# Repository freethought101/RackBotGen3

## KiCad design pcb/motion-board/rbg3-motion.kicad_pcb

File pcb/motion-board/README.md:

# RBG3-MOTION v1 — robot motion board

2-layer, 100 × 100 mm module carrier: ESP32-S3-DevKitC-1 + 4 × TMC2209 StepStick drivers,
switch inputs, servo/LED/buzzer/I2C outputs, VMOT and dock voltage sensing.
Spec: [`docs/spec/02-electrical.md`](../../docs/spec/02-electrical.md) §3.

| File | What |
|---|---|
| `rbg3-motion.kicad_sch` / `.kicad_pcb` / `.kicad_pro` | KiCad 10 project (schematic ERC clean, DRC: 0 errors, 0 unconnected, 0 parity) |
| `lib/rbg3.kicad_sym`, `lib/rbg3.pretty/` | Custom symbols (`ESP32-S3-DevKitC-1`, `StepStick_TMC2209`) and the DevKit socket footprint |
| `scripts/build.sh` | Rebuilds the layout from scratch: text fix-ups → placement → silkscreen (`silk.py`) → antenna keep-out → Freerouting (GND routed as tracks too, so traces cannot cut a pour pocket loose) → stitching vias → pours → DRC; fails on unrouted nets or any error-level DRC item |
| `fab/rbg3-motion-gerbers.zip` | Gerbers + Excellon drill (separate PTH / NPTH files) for JLCPCB (2 layers, 1.6 mm, 1 oz, HASL is fine) |
| `fab/rbg3-motion-bom.csv`, `fab/rbg3-motion-pos.csv` | BOM and placement file (hand assembly expected: 0805 / SOT-23 / SOD-123 / SMB + through-hole) |
| `fab/rbg3-motion-jlc-bom.csv`, `fab/rbg3-motion-jlc-cpl.csv` | JLCPCB **Economic** assembly of the 45 SMD parts on 2 of the 5 boards (the plan since spec v0.1.20) (LCSC numbers in `scripts/jlc_pcba.py`; all basic or preferred, so no extended-part fees). Check Q1, D1 and D2 orientation in the placement preview |
| `fab/rbg3-motion-schematic.pdf`, `fab/rbg3-motion.step` | Schematic print and 3D board for the robot CAD |

Rebuild: `scripts/build.sh` (needs KiCad 10 at `/Applications/KiCad`, Java 21+, Freerouting jar at
`~/.kicad-mcp/freerouting.jar` or `$FREEROUTING_JAR`). Then `scripts/export_fab.sh` regenerates `fab/`.

## Board summary

- **Power in**: J1 XT30 **VMOT** after the robot E-stop (**pad 2 = +, pad 1 = −**, matches the XT30 silkscreen), bottom-left
  corner, mating face 1.7 mm past the board edge so the plug goes in from outside,
  J2 **5 V** from the off-board 5 V/5 A buck, J3 **6 V servo** from the off-board 6 V/3 A buck.
  Bulk 470 µF + **SMBJ18A** unidirectional TVS right at J1 (cathode on VMOT: clamps ringing, and a reversed harness
  conducts and blows the 7.5 A fuse); 100 µF + 100 nF at every driver. 220 µF + 100 nF on the servo rail
  (C18/C19), 10 µF + 100 nF on +5V (C20/C21) and on +3V3 (C22/C23).
- **Test pads** TP1–TP7 (SMD, Ø 2 mm): VM, 5V, 6V, 3V3 between the drive L/R sockets; UART, EN, GND by R5/R6.
- **J13 (AUX)** takes the robot E-stop's NO contact (pressed = low): the firmware reports the press at once.
- **ESP32**: powered over USB from the Pi; its 5V pin is **not** connected. 3V3 from the DevKit feeds logic.
  Use a **90° USB-C plug** whose cable exits away from the board: the area under the USB end (y 179.5–191) is kept
  free of connectors (J12/J13 sit left of it), but J10/J11 on the bottom edge are ≈ 13 mm from the port.
- **Drivers**: UART addresses hard-wired with MS1/MS2: U2 drive-L = 0, U3 drive-R = 1, U4 Z = 2, U5 Y = 3.
  Single-wire UART on StepStick pin 4 (PDN_UART): ESP TX (GPIO9) via 1 k, RX (GPIO10) direct. CLK tied to GND.
  **JP1–JP4** (normally bridged solder jumpers between the socket rows, labelled `JPn P5 CUT`) join pin 5 to the bus,
  as the MKS TMC2209 V2.0 needs. Cut the copper strip only for a module with another signal on pin 5 (module unplugged).
- **Inputs** (J8–J13, JST-XH GND/SIG/3V3): Z_HOME, Y_HOME, NOSE, SLOT_A, SLOT_B, AUX — 10 k pull-up, 1 k series, 100 nF.
- **Outputs**: servos J14/J15 (GND, 6V, SIG, 330 Ω), WS2812 J17, buzzer J19 (low-side NPN), I2C J16 (INA226).
- **Sense**: VMOT 100 k/18 k → GPIO1 (16.8 V → 2.56 V), dock 100 k/10 k → GPIO2 (J18 pin 1; wire it to the dock + pad
  **before** the SS54, so the charger cannot backfeed it). J18 pin 2 is **not connected**: never wire dock − to the
  robot, because it goes only to the charger IN−. Home switches (J8/J9) are wired NC for fail-safe homing.
- Net classes: VMOT, GND and +6V_SERVO 1.0 mm; motor 0.6 mm; +5V/+3V3 0.5 mm; signals 0.25 mm.
- GND stitching vias on a 5 mm grid, plus one next to every through-hole GND pad that has none nearby.
  Copper keep-out under the DevKit antenna (top-right corner).
- **Silkscreen** (`scripts/silk.py`): the board name, plus function and pin order at every connector. Each StepStick socket
  has its module pin names at the corners (EN/VM at the top, DIR/GND at the bottom), and the DevKit socket is marked
  ANTENNA END / USB END, and the XT30 (J1) has + / − marks above its pads. The reference designators of J8–J15 and JP1–JP4 are on F.Fab; the function labels name those parts.

## Check before ordering (things drawn from memory, not datasheets)

1. **DevKit header row spacing.** The right-hand row is drilled at **both 22.86 mm and 25.4 mm** from the left row.
   Measure your ESP32-S3-DevKitC-1 and solder the female header into the matching row only.
2. **DevKit pinout.** Compare `lib/rbg3.kicad_sym` (J1 = pins 1–22, J3 = pins 23–44, pin 1 at the antenna end)
   against Espressif's ESP32-S3-DevKitC-1 pin layout for your board revision.
3. **StepStick pinout.** Left column EN, MS1, MS2, PDN_UART, PDN_UART2, CLK, STEP, DIR; right column VM, GND,
   2B, 2A, 1A, 1B, VDD, GND (Pololu layout). Check your TMC2209 module's silkscreen, especially pin 4 vs 5 for UART.
   JP1–JP4 come bridged (UART on pin 4 and 5); cut one only if that module uses pin 5 for something else. Insert each module so its EN pin matches the `EN` mark.
4. **Motor connector order** is 2B, 2A, 1A, 1B. If a motor runs backwards or stutters, swap one coil pair in the cable.
5. **Mounting holes**: M3 at 93 × 93 mm pitch (3.5 mm from each edge).

## Assembly and bring-up checklist

JLCPCB fits the 45 SMD parts on 2 of the 5 boards (Economic PCBA); the through-hole parts and the 3 bare
spares are hand-soldered. Tools: fine-tip iron, flux, 0.5–0.8 mm solder, tweezers,
multimeter, current-limited bench supply.

**Solder, low parts first so the board sits flat**

*JLCPCB-assembled boards: the first two items are already done; check them by eye and start at JP1–JP4.
Only the 3 bare spares need them.*

- [ ] 0805 resistors and capacitors (values in `fab/rbg3-motion-bom.csv`).
- [ ] Q1 MMBT3904 (SOT-23), D2 1N4148W (SOD-123, band as on the silkscreen), D1 SMBJ18A (SMB, **band toward VMOT**).
- [ ] JP1–JP4: check with a meter that each joins pin 5 to the UART bus (bridged on the board; nothing to solder for the MKS TMC2209 V2.0).
      Easiest before the sockets go on; always with the module unplugged.
- [ ] Through-hole, low to tall: J14/J15 servo headers → JST-XH (J4–J13, J16–J19) → StepStick sockets (8 rows) →
      DevKit female headers (**matching row only**, 22.86 or 25.4 mm) → J2/J3 terminals → J1 XT30 →
      electrolytics C1/C3/C5/C7/C9/C18 last (**long leg to the + pad**; C18 is the 220 µF / 25 V servo-rail cap).
- [ ] Clean the flux and look for bridges, especially at Q1, the socket rows and the DevKit rows.

**Harness polarity, before the first plug-in** (nothing on the board blocks a reversed lead, spec 02 §3)

- [ ] Use ready-made XT30/XT60 pigtails (leads soldered at the factory) and wire by colour only: red = +, black = −.
- [ ] Meter every finished lead on its mating pins: + must land on J1 pad 2 (the `+` mark next to J1). Check the
      battery pack's XT60 from the shop the same way.
- [ ] The first power-up is always the bench supply below, never the battery.

**Bring-up, stop at the first failure**

- [ ] Nothing plugged in: no short from VMOT, +5V, +6V_SERVO or +3V3 to GND.
- [ ] Bench supply 16.8 V, limit 0.2 A, into J1 (pad 2 = +): idle current near zero, VMOT on all four VM pins,
      nothing warm. Don't test reverse polarity (by design it blows the 7.5 A fuse through D1).
- [ ] Set and check the 5.0 V and 5.8 V (servo, "6V" rail) bucks off-board before wiring them to J2/J3. Check the
      polarity of both leads with a meter before tightening the terminals (J2/J3 are not reverse-protected), then
      read 5.0 V and 5.8 V at TP2 and TP3.
- [ ] ESP32 in, powered over USB (its 5V pin is not used): GPIO1 reads ≈ 2.56 V at 16.8 V; each input J8–J13 toggles
      (home switches are NC, so they read active until pressed). Press the E-stop: TEL `sw` bit5 sets at once.
- [ ] **VMOT off**, then fit the TMC2209s (EN pin at the `EN` mark) and connect the motors. Never plug or unplug a
      driver or a motor with VMOT on. Power up; the firmware sets motor current over UART. Check that addresses 0–3
      answer, then jog each axis slowly (motor wrong way or stuttering: swap one coil pair in its cable).

## Known cosmetic items

DRC reports 16 silkscreen-only items (reference designators touching each other or the C9 outline, the "DOCK+ V+ NC" label
touching a C20 pad, and the J1 outline clipped by the board edge). JLCPCB clips silkscreen over pads automatically; tidy them in the KiCad PCB editor if wanted. It also reports 8
`lib_footprint_mismatch` warnings, both changed on purpose in `scripts/fix_text.py`: JP1–JP4 have their courtyards
removed, and the StepStick sockets U2–U5 are drilled 1.0 mm instead of the library's 0.8 mm so female-header tails fit.

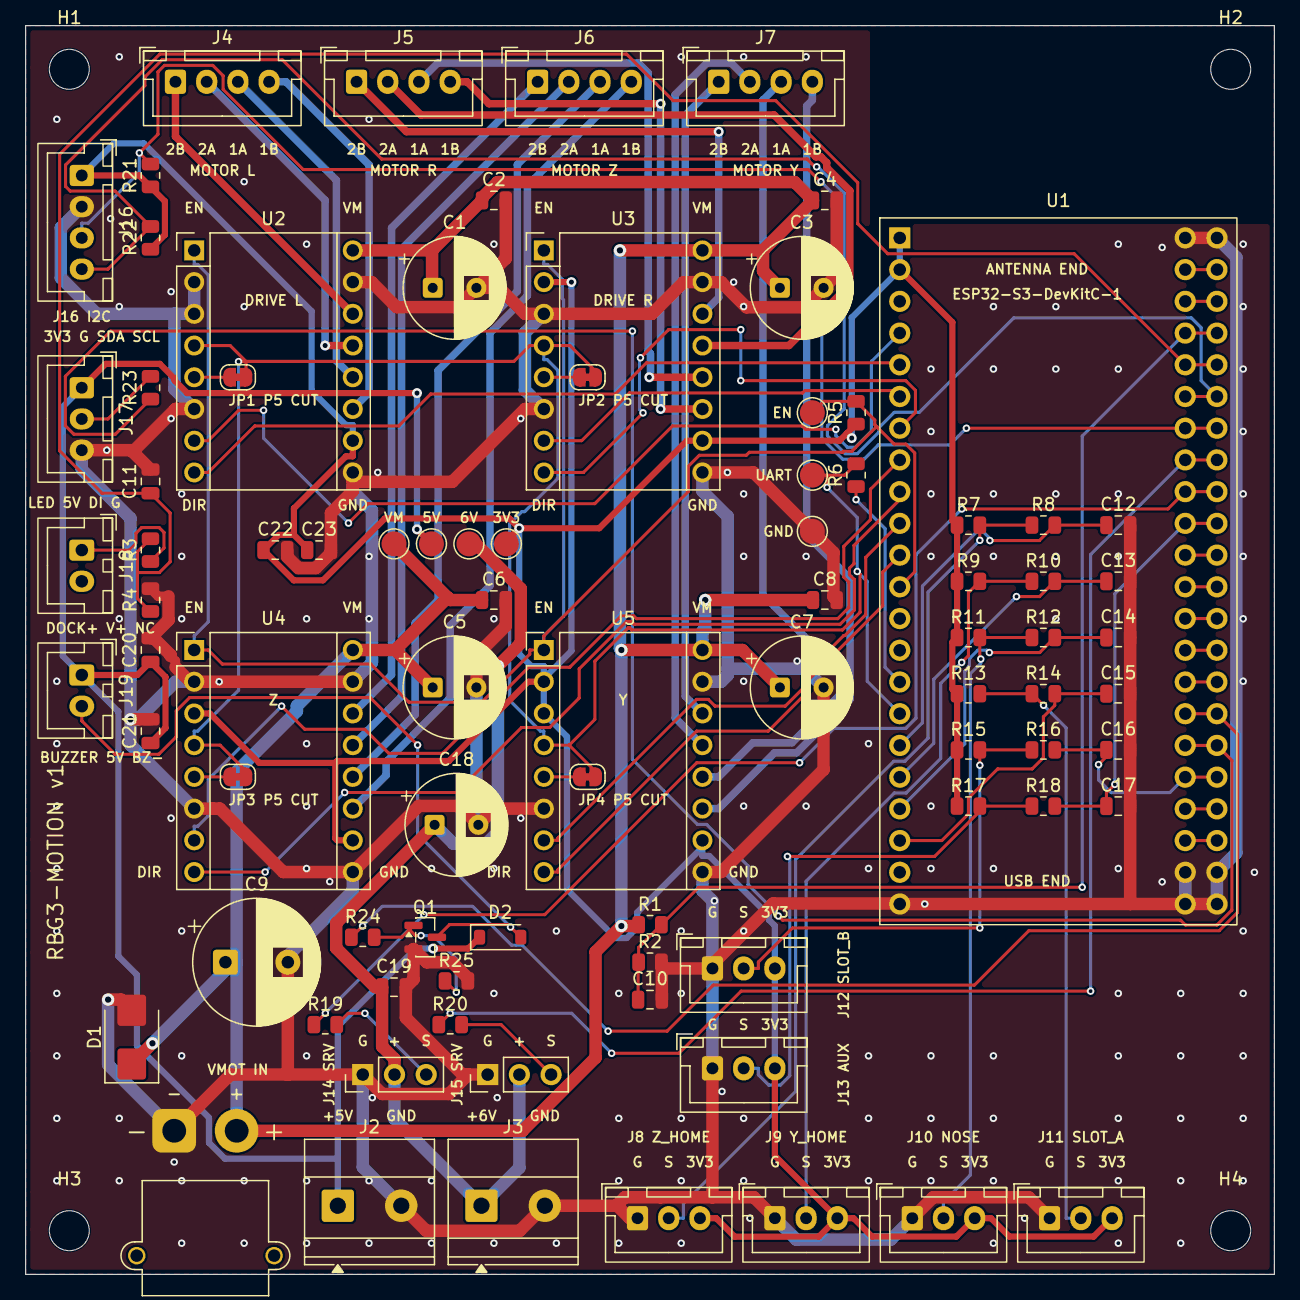
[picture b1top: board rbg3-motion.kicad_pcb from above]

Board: 2 copper layers, 100.0 x 100.0 mm, 90 parts (0 on the bottom side), 62 nets.

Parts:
C1, C3, C5, C7: 100uF 35V; CP_Radial_D8.0mm_P3.50mm
C2, C4, C6, C8, C10, C11, C12, C13, C14, C15, C16, C17, C19, C21, C23: 100nF; C_0805_2012Metric
C9: 470uF 35V; CP_Radial_D10.0mm_P5.00mm
C18: 220uF 25V; CP_Radial_D8.0mm_P3.50mm
C20, C22: 10uF; C_0805_2012Metric
D1: SMBJ18A; D_SMB
D2: 1N4148W; D_SOD-123
H1, H2, H3, H4: M3; MountingHole_3.2mm_M3
J1: VMOT_IN XT30 (after E-stop); AMASS_XT30PW-M_1x02_P2.50mm_Horizontal
J2: 5V_IN (from 5V buck); TerminalBlock_Phoenix_MKDS-1,5-2-5.08_1x02_P5.08mm_Horizont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
J3: 6V_SERVO_IN (from 6V buck); TerminalBlock_Phoenix_MKDS-1,5-2-5.08_1x02_P5.08mm_Horizont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
J4: MOTOR_L; JST_XH_B4B-XH-A_1x04_P2.50mm_Vertical
J5: MOTOR_R; JST_XH_B4B-XH-A_1x04_P2.50mm_Vertical
J6: MOTOR_Z; JST_XH_B4B-XH-A_1x04_P2.50mm_Vertical
J7: MOTOR_Y; JST_XH_B4B-XH-A_1x04_P2.50mm_Vertical
J8: SW_Z_HOME; JST_XH_B3B-XH-A_1x03_P2.50mm_Vertical
J9: SW_Y_HOME; JST_XH_B3B-XH-A_1x03_P2.50mm_Vertical
J10: SW_NOSE; JST_XH_B3B-XH-A_1x03_P2.50mm_Vertical
J11: SW_SLOT_A; JST_XH_B3B-XH-A_1x03_P2.50mm_Vertical
J12: SW_SLOT_B; JST_XH_B3B-XH-A_1x03_P2.50mm_Vertical
J13: SW_AUX_IN; JST_XH_B3B-XH-A_1x03_P2.50mm_Vertical
J14: SERVO_A (GND,6V,SIG); PinHeader_1x03_P2.54mm_Vertical
J15: SERVO_B (GND,6V,SIG); PinHeader_1x03_P2.54mm_Vertical
J16: I2C INA226 (3V3,GND,SDA,SCL); JST_XH_B4B-XH-A_1x04_P2.50mm_Vertical
J17: WS2812 (5V,DIN,GND); JST_XH_B3B-XH-A_1x03_P2.50mm_Vertical
J18: DOCK_V+ (dock + pad, before SS54; pin 2 NC); JST_XH_B2B-XH-A_1x02_P2.50mm_Vertical
J19: BUZZER (5V, low-side); JST_XH_B2B-XH-A_1x02_P2.50mm_Vertical
JP1, JP2, JP3, JP4: UART_PIN5 (bridged); SolderJumper-2_P1.3mm_Bridged_RoundedPad1.0x1.5mm
Q1: MMBT3904; SOT-23
R1, R3: 100k; R_0805_2012Metric
R2: 18k; R_0805_2012Metric
R4, R5, R7, R9, R11, R13, R15, R17, R25: 10k; R_0805_2012Metric
R6, R8, R10, R12, R14, R16, R18, R24: 1k; R_0805_2012Metric
R19, R20, R23: 330; R_0805_2012Metric
R21, R22: 4.7k; R_0805_2012Metric
TP1, TP2, TP3, TP4, TP5, TP6, TP7: TestPoint; TestPoint_Pad_D2.0mm
U1: ESP32-S3-DevKitC-1; ESP32-S3-DevKitC-1_Socket
U2: TMC2209 DRV_L addr0; Pololu_Breakout-16_15.2x20.3mm
U3: TMC2209 DRV_R addr1; Pololu_Breakout-16_15.2x20.3mm
U4: TMC2209 Z addr2; Pololu_Breakout-16_15.2x20.3mm
U5: TMC2209 Y addr3; Pololu_Breakout-16_15.2x20.3mm

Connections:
/+3V3: C22.1, C23.1, J8.3, J9.3, J10.3, J11.3, J12.3, J13.3, J16.1, R5.1, R7.1, R9.1, R11.1, R13.1, R15.1, R17.1, R21.1, R22.1, TP4.1, U1.1, U1.2, U2.10, U3.2, U3.10, U4.3, U4.10, U5.2, U5.3, U5.10
/+5V: C20.1, C21.1, D2.1, J2.1, J17.1, J19.1, TP2.1
/+6V_SERVO: C18.1, C19.1, J3.1, J14.2, J15.2, TP3.1
/AUX_IN: C17.1, R18.2, U1.32
/AUX_IN_RAW: J13.2, R17.2, R18.1
/BUZZER: R24.1, U1.38
/BUZ_B: Q1.1, R24.2, R25.1
/BUZ_N: D2.2, J19.2, Q1.3
/DOCK_V_IN: J18.1, R3.1
/DOCK_V_SENSE: C11.1, R3.2, R4.1, U1.27
/DRV_L_DIR: U1.5, U2.8
/DRV_L_STEP: U1.4, U2.7
/DRV_R_DIR: U1.7, U3.8
/DRV_R_STEP: U1.6, U3.7
/GND: C1.2, C2.2, C3.2, C4.2, C5.2, C6.2, C7.2, C8.2, C9.2, C10.2, C11.2, C12.2, C13.2, C14.2, C15.2, C16.2, C17.2, C18.2, C19.2, C20.2, C21.2, C22.2, C23.2, D1.2, J1.1, J2.2, J3.2, J8.1, J9.1, J10.1, J11.1, J12.1, J13.1, J14.1, J15.1, J16.2, J17.3, Q1.2, R2.2, R4.2, R25.2, TP7.1, U1.22, U1.23, U1.43, U1.44, U2.2, U2.3, U2.6, U2.9, U2.15, U3.3, U3.6, U3.9, U3.15, U4.2, U4.6, U4.9, U4.15, U5.6, U5.9, U5.15
/I2C_SCL: J16.4, R22.2, U1.28
/I2C_SDA: J16.3, R21.2, U1.29
/LED_DIN: J17.2, R23.2
/ML_1A: J4.3, U2.12
/ML_1B: J4.4, U2.11
/ML_2A: J4.2, U2.13
/ML_2B: J4.1, U2.14
/MR_1A: J5.3, U3.12
/MR_1B: J5.4, U3.11
/MR_2A: J5.2, U3.13
/MR_2B: J5.1, U3.14
/MY_1A: J7.3, U5.12
/MY_1B: J7.4, U5.11
/MY_2A: J7.2, U5.13
/MY_2B: J7.1, U5.14
/MZ_1A: J6.3, U4.12
/MZ_1B: J6.4, U4.11
/MZ_2A: J6.2, U4.13
/MZ_2B: J6.1, U4.14
/NOSE: C14.1, R12.2, U1.19
/NOSE_RAW: J10.2, R11.2, R12.1
/SERVO_A: R19.1, U1.31
/SERVO_A_OUT: J14.3, R19.2
/SERVO_B: R20.1, U1.30
/SERVO_B_OUT: J15.3, R20.2
/SLOT_A: C15.1, R14.2, U1.20
/SLOT_A_RAW: J11.2, R13.2, R14.1
/SLOT_B: C16.1, R16.2, U1.40
/SLOT_B_RAW: J12.2, R15.2, R16.1
/STATUS_LED: R23.1, U1.39
/STEPPER_EN_N: R5.2, TP6.1, U1.12, U2.1, U3.1, U4.1, U5.1
/TMC_UART: JP1.1, JP2.1, JP3.1, JP4.1, R6.2, TP5.1, U1.16, U2.4, U3.4, U4.4, U5.4
/TMC_UART_TX: R6.1, U1.15
/UART_P5_U2: JP1.2, U2.5
/UART_P5_U3: JP2.2, U3.5
/UART_P5_U4: JP3.2, U4.5
/UART_P5_U5: JP4.2, U5.5
/VMOT: C1.1, C2.1, C3.1, C4.1, C5.1, C6.1, C7.1, C8.1, C9.1, D1.1, J1.2, R1.1, TP1.1, U2.16, U3.16, U4.16, U5.16
/VMOT_SENSE: C10.1, R1.2, R2.1, U1.26
/Y_DIR: U1.11, U5.8
/Y_HOME: C13.1, R10.2, U1.18
/Y_HOME_RAW: J9.2, R9.2, R10.1
/Y_STEP: U1.10, U5.7
/Z_DIR: U1.9, U4.8
/Z_HOME: C12.1, R8.2, U1.17
/Z_HOME_RAW: J8.2, R7.2, R8.1
/Z_STEP: U1.8, U4.7

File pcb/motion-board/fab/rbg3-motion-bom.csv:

"Reference","Value","Footprint","QUANTITY","DNP"
"C1,C3,C5,C7","100uF 35V","Capacitor_THT:CP_Radial_D8.0mm_P3.50mm","4",""
"C2,C4,C6,C8,C10-C17,C19,C21,C23","100nF","Capacitor_SMD:C_0805_2012Metric","15",""
"C9","470uF 35V","Capacitor_THT:CP_Radial_D10.0mm_P5.00mm","1",""
"C18","220uF 25V","Capacitor_THT:CP_Radial_D8.0mm_P3.50mm","1",""
"C20,C22","10uF","Capacitor_SMD:C_0805_2012Metric","2",""
"D1","SMBJ18A","Diode_SMD:D_SMB","1",""
"D2","1N4148W","Diode_SMD:D_SOD-123","1",""
"J1","VMOT_IN XT30 (after E-stop)","Connector_AMASS:AMASS_XT30PW-M_1x02_P2.50mm_Horizontal","1",""
"J2","5V_IN (from 5V buck)","TerminalBlock_Phoenix:TerminalBlock_Phoenix_MKDS-1,5-2-5.08_1x02_P5.08mm_Horizontal","1",""
"J3","6V_SERVO_IN (from 6V buck)","TerminalBlock_Phoenix:TerminalBlock_Phoenix_MKDS-1,5-2-5.08_1x02_P5.08mm_Horizontal","1",""
"J4","MOTOR_L","Connector_JST:JST_XH_B4B-XH-A_1x04_P2.50mm_Vertical","1",""
"J5","MOTOR_R","Connector_JST:JST_XH_B4B-XH-A_1x04_P2.50mm_Vertical","1",""
"J6","MOTOR_Z","Connector_JST:JST_XH_B4B-XH-A_1x04_P2.50mm_Vertical","1",""
"J7","MOTOR_Y","Connector_JST:JST_XH_B4B-XH-A_1x04_P2.50mm_Vertical","1",""
"J8","SW_Z_HOME","Connector_JST:JST_XH_B3B-XH-A_1x03_P2.50mm_Vertical","1",""
"J9","SW_Y_HOME","Connector_JST:JST_XH_B3B-XH-A_1x03_P2.50mm_Vertical","1",""
"J10","SW_NOSE","Connector_JST:JST_XH_B3B-XH-A_1x03_P2.50mm_Vertical","1",""
"J11","SW_SLOT_A","Connector_JST:JST_XH_B3B-XH-A_1x03_P2.50mm_Vertical","1",""
"J12","SW_SLOT_B","Connector_JST:JST_XH_B3B-XH-A_1x03_P2.50mm_Vertical","1",""
"J13","SW_AUX_IN","Connector_JST:JST_XH_B3B-XH-A_1x03_P2.50mm_Vertical","1",""
"J14","SERVO_A (GND,6V,SIG)","Connector_PinHeader_2.54mm:PinHeader_1x03_P2.54mm_Vertical","1",""
"J15","SERVO_B (GND,6V,SIG)","Connector_PinHeader_2.54mm:PinHeader_1x03_P2.54mm_Vertical","1",""
"J16","I2C INA226 (3V3,GND,SDA,SCL)","Connector_JST:JST_XH_B4B-XH-A_1x04_P2.50mm_Vertical","1",""
"J17","WS2812 (5V,DIN,GND)","Connector_JST:JST_XH_B3B-XH-A_1x03_P2.50mm_Vertical","1",""
"J18","DOCK_V+ (dock + pad, before SS54; pin 2 NC)","Connector_JST:JST_XH_B2B-XH-A_1x02_P2.50mm_Vertical","1",""
"J19","BUZZER (5V, low-side)","Connector_JST:JST_XH_B2B-XH-A_1x02_P2.50mm_Vertical","1",""
"Q1","MMBT3904","Package_TO_SOT_SMD:SOT-23","1",""
"R1,R3","100k","Resistor_SMD:R_0805_2012Metric","2",""
"R2","18k","Resistor_SMD:R_0805_2012Metric","1",""
"R4,R5,R7,R9,R11,R13,R15,R17,R25","10k","Resistor_SMD:R_0805_2012Metric","9",""
"R6,R8,R10,R12,R14,R16,R18,R24","1k","Resistor_SMD:R_0805_2012Metric","8",""
"R19,R20,R23","330","Resistor_SMD:R_0805_2012Metric","3",""
"R21,R22","4.7k","Resistor_SMD:R_0805_2012Metric","2",""
"U1","ESP32-S3-DevKitC-1","rbg3:ESP32-S3-DevKitC-1_Socket","1",""
"U2","TMC2209 DRV_L addr0","Module:Pololu_Breakout-16_15.2x20.3mm","1",""
"U3","TMC2209 DRV_R addr1","Module:Pololu_Breakout-16_15.2x20.3mm","1",""
"U4","TMC2209 Z addr2","Module:Pololu_Breakout-16_15.2x20.3mm","1",""
"U5","TMC2209 Y addr3","Module:Pololu_Breakout-16_15.2x20.3mm","1",""

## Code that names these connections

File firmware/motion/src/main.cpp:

// RBG3-MOTION firmware: ESP32-S3 implementation of the rbg3::Hal and the main loop.
// All protocol, interlock and safety logic lives in lib/rbg3core (host-tested).
#include <Adafruit_NeoPixel.h>
#include <Arduino.h>
#include <ESP32Servo.h>
#include <FastAccelStepper.h>
#include <INA226.h>
#include <TMCStepper.h>
#include <Wire.h>

#include "controller.h"
#include "pins.h"

using namespace rbg3;

namespace {

constexpr int kStepPins[AX_COUNT] = {pins::L_STEP, pins::R_STEP, pins::Z_STEP, pins::Y_STEP};
constexpr int kDirPins[AX_COUNT] = {pins::L_DIR, pins::R_DIR, pins::Z_DIR, pins::Y_DIR};
constexpr uint8_t kTmcAddr[AX_COUNT] = {0, 1, 2, 3};  // MS1/MS2 straps per socket (02 §2)
#ifdef RBG3_RIG
// Table rig: only the Z (U4) and Y (U5) sockets are fitted. An empty socket never answers over UART, so
// configureDrivers() would always fail and the board would never leave E-stop.
constexpr bool kDriverFitted[AX_COUNT] = {false, false, true, true};
#else
constexpr bool kDriverFitted[AX_COUNT] = {true, true, true, true};
#endif

class EspHal : public Hal {
 public:
  void begin() {
    pinMode(pins::STEPPER_EN_N, OUTPUT);
    digitalWrite(pins::STEPPER_EN_N, HIGH);  // disabled
    for (int p : {pins::Z_HOME, pins::Y_HOME, pins::NOSE, pins::SLOT_A, pins::SLOT_B, pins::AUX_IN})
      pinMode(p, INPUT_PULLUP);
    pinMode(pins::BUZZER, OUTPUT);
    digitalWrite(pins::BUZZER, LOW);
    analogReadResolution(12);

    engine_.init();
    for (int i = 0; i < AX_COUNT; i++) {
      steppers_[i] = engine_.stepperConnectToPin(kStepPins[i]);
      if (steppers_[i]) steppers_[i]->setDirectionPin(kDirPins[i], DIR_HIGH_COUNTS_UP[i]);
    }

    Serial1.begin(115200, SERIAL_8N1, pins::TMC_RX, pins::TMC_TX);
    for (int i = 0; i < AX_COUNT; i++) drivers_[i] = new TMC2209Stepper(&Serial1, TMC_R_SENSE, kTmcAddr[i]);

    Wire.begin(pins::I2C_SDA, pins::I2C_SCL);
    ina_ok_ = ina_.begin() && ina_.setMaxCurrentShunt(INA_MAX_A, INA_SHUNT_OHM) == INA226_ERR_NONE;
    ina_.setAverage(INA226_16_SAMPLES);

    ESP32PWM::allocateTimer(0);
    for (int i = 0; i < 2; i++) {
      servos_[i].setPeriodHertz(50);
      servos_[i].attach(i == 0 ? pins::SERVO_A : pins::SERVO_B, 500, 2400);
    }

    pixel_.begin();
    pixel_.setBrightness(40);
  }

  uint32_t millis() override { return ::millis(); }

  void moveTo(Axis a, int32_t pos, uint32_t speed_hz, uint32_t accel) override {
    auto* s = steppers_[a];
    if (!s) return;
    s->setSpeedInHz(speed_hz);
    s->setAcceleration(accel);
    s->moveTo(pos);
  }

  void runAt(Axis a, int32_t speed_hz, uint32_t accel) override {
    auto* s = steppers_[a];
    if (!s) return;
    if (speed_hz == 0) return s->stopMove();
    s->setSpeedInHz(static_cast<uint32_t>(abs(speed_hz)));
    s->setAcceleration(accel);
    if (s->isRunning()) s->applySpeedAcceleration();
    if (speed_hz > 0) {
      s->runForward();
    } else {
      s->runBackward();
    }
  }

  void stop(Axis a) override {
    if (steppers_[a]) steppers_[a]->stopMove();
  }
  void halt(Axis a) override {
    if (steppers_[a]) steppers_[a]->forceStop();
  }
  bool running(Axis a) override { return steppers_[a] && steppers_[a]->isRunning(); }
  int32_t position(Axis a) override { return steppers_[a] ? steppers_[a]->getCurrentPosition() : 0; }
  void setPosition(Axis a, int32_t pos) override {
    if (steppers_[a]) steppers_[a]->setCurrentPosition(pos);
  }

  void enableDrivers(bool on) override { digitalWrite(pins::STEPPER_EN_N, on ? LOW : HIGH); }

  bool configureDrivers(const DriverSettings& cfg) override {
    bool ok = true;
    for (int i = 0; i < AX_COUNT; i++) {
      if (!kDriverFitted[i]) continue;
      TMC2209Stepper& d = *drivers_[i];
      uint8_t before = d.IFCNT();
      d.begin();
      d.toff(4);
      d.blank_time(24);
      d.I_scale_analog(false);  // current from UART, not the VREF pot
      d.internal_Rsense(false);
      d.pdn_disable(true);       // PDN_UART pin is used for UART
      d.mstep_reg_select(true);  // microsteps from MRES, not the MS1/MS2 address straps
      d.microsteps(cfg.microsteps);
      d.intpol(true);
      float hold = i == AX_Z ? static_cast<float>(cfg.hold_ma_z) / cfg.run_ma[i] : 0.5f;
      d.rms_current(cfg.run_ma[i], hold);
      d.en_spreadCycle(false);  // StealthChop
      d.pwm_autoscale(true);
      d.GSTAT(0b111);  // clear reset / drv_err / uv_cp flags
      uint8_t after = d.IFCNT();
      // Every successful write increments IFCNT; no change means the driver did not hear us.
      if (after == before || d.microsteps() != cfg.microsteps) ok = false;
    }
    return ok;
  }

  bool driversWereReset() override {
    bool reset = false;
    for (int i = 0; i < AX_COUNT; i++)
      if (kDriverFitted[i]) reset |= (drivers_[i]->GSTAT() & 0x01) != 0;
    return reset;
  }

  Inputs inputs() override {
    Inputs in;
    in.z_home = digitalRead(pins::Z_HOME) == HIGH;
    in.y_home = digitalRead(pins::Y_HOME) == HIGH;
    in.nose = digitalRead(pins::NOSE) == LOW;
    in.slot_a = digitalRead(pins::SLOT_A) == LOW;
    in.slot_b = digitalRead(pins::SLOT_B) == LOW;
    in.estop = digitalRead(pins::AUX_IN) == LOW;
    return in;
  }

  float vmot() override { return analogReadMilliVolts(pins::VMOT_SENSE) / 1000.0f * VMOT_DIVIDER; }
  float dockV() override { return analogReadMilliVolts(pins::DOCK_SENSE) / 1000.0f * DOCK_DIVIDER; }

  // The INA226 is read at 10 Hz (cached): I2C on every loop pass would slow down the control loop.
  float vbat() override {
    refreshIna();
    return vbat_;
  }
  float ibat() override {
    refreshIna();
    return ibat_;
  }

  void servo(uint8_t i, float deg) override {
    if (i < 2) servos_[i].write(static_cast<int>(deg));
  }

  void led(Led state) override {
    uint32_t c = 0;
    bool blink = (::millis() / 250) % 2;
    switch (state) {
      case Led::OFF: c = 0; break;
      case Led::IDLE: c = pixel_.Color(0, 0, 255); break;
      case Led::DOCKED: c = pixel_.Color(0, 255, 0); break;
      case Led::MOVING: c = pixel_.Color(255, 160, 0); break;
      case Led::FAULT: c = pixel_.Color(255, 0, 0); break;
      case Led::ESTOP: c = blink ? pixel_.Color(255, 0, 0) : 0; break;
    }
    if (c != last_color_) {
      last_color_ = c;
      pixel_.setPixelColor(0, c);
      pixel_.show();
    }
    bool beep = state == Led::ESTOP && blink && (::millis() / 2000) % 5 == 0;  // short chirp every 10 s
    digitalWrite(pins::BUZZER, beep ? HIGH : LOW);
  }

  void writeLine(const char* line) override {
    Serial.print(line);
    Serial.print('\n');
  }

 private:
  void refreshIna() {
    if (!ina_ok_ || ::millis() - ina_t_ < 100) return;
    ina_t_ = ::millis();
    vbat_ = ina_.getBusVoltage();
    ibat_ = ina_.getCurrent();
  }

  FastAccelStepperEngine engine_;
  FastAccelStepper* steppers_[AX_COUNT] = {};
  TMC2209Stepper* drivers_[AX_COUNT] = {};
  INA226 ina_{INA_ADDR};
  bool ina_ok_ = false;
  uint32_t ina_t_ = 0;
  float vbat_ = 0, ibat_ = 0;
  Servo servos_[2];
  Adafruit_NeoPixel pixel_{1, pins::STATUS_LED, NEO_GRB + NEO_KHZ800};
  uint32_t last_color_ = 1;
};

EspHal hal;
Controller controller(hal);

}  // namespace

void setup() {
  Serial.begin(115200);
  Serial.setTxTimeoutMs(0);  // never block the control loop when the Pi is not reading
  hal.begin();
  controller.begin();
}

void loop() {
  while (Serial.available() > 0) controller.feed(static_cast<char>(Serial.read()));
  controller.update();
}
